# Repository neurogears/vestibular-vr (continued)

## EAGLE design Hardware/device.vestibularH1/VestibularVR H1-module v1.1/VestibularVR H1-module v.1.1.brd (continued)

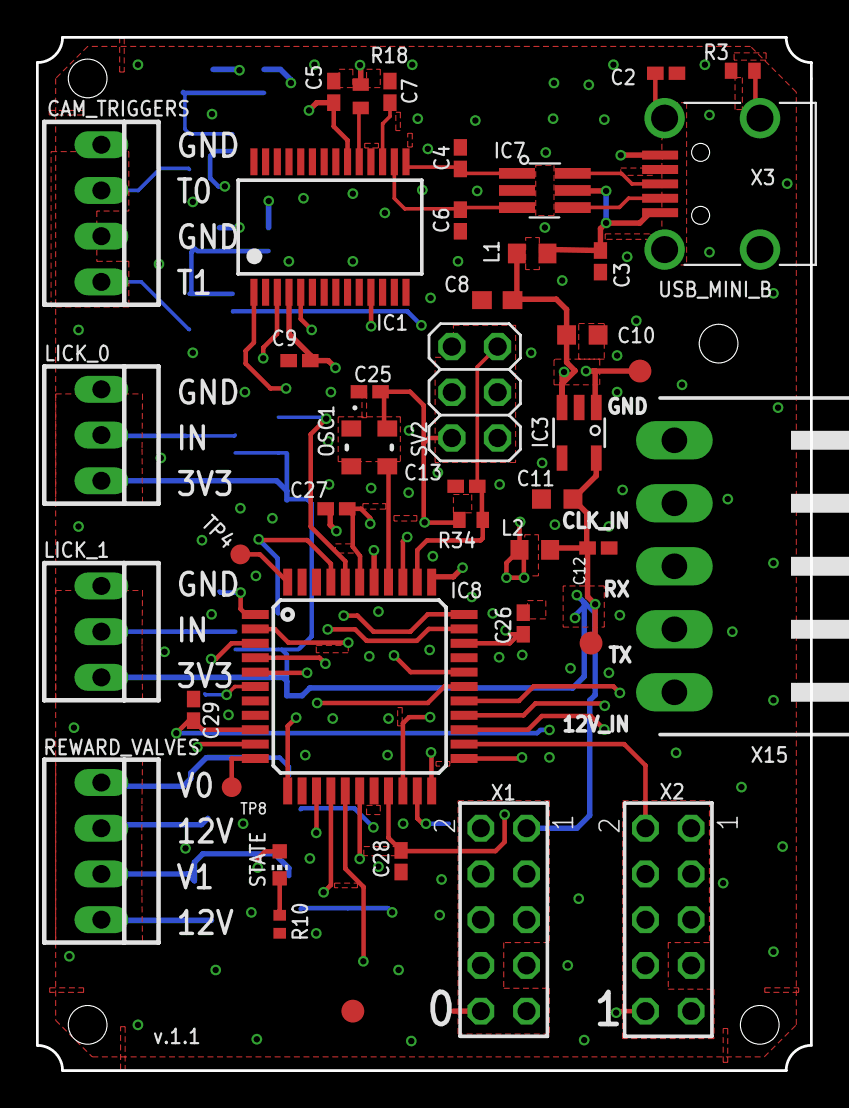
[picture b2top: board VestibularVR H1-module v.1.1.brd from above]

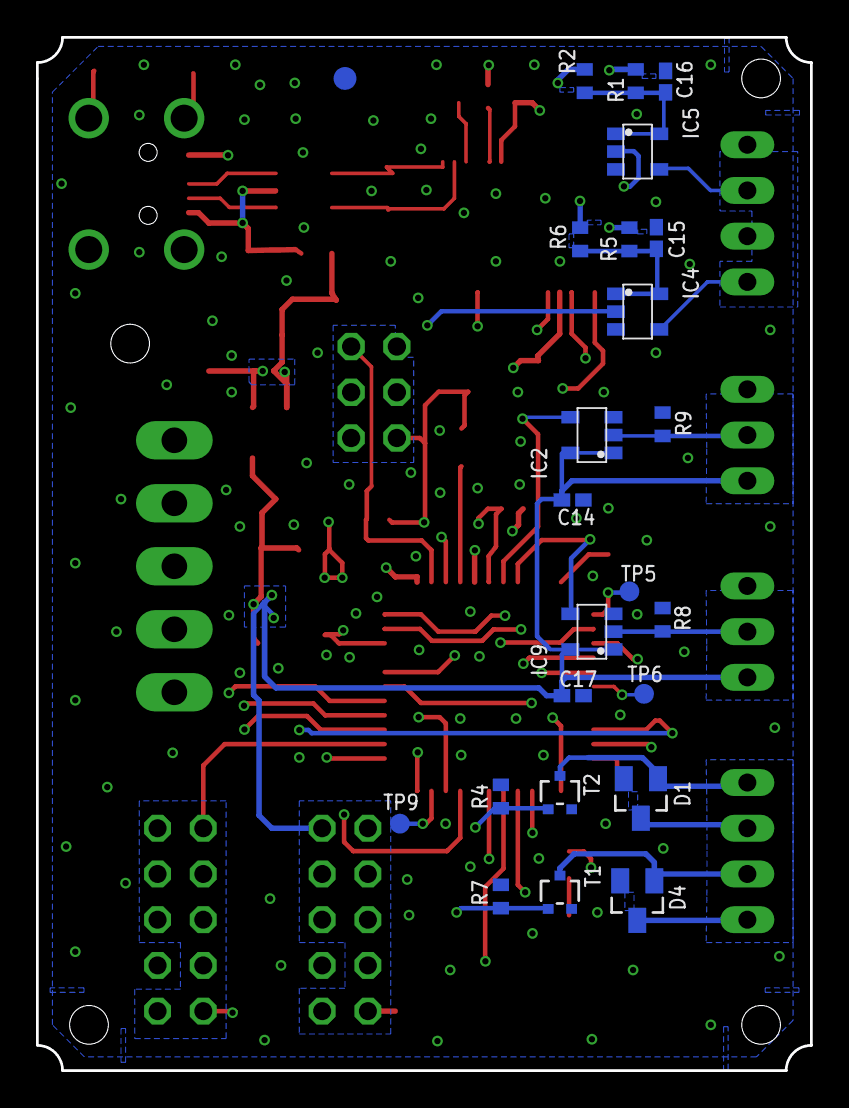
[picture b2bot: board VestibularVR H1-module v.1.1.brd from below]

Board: 4 copper layers, 43.0 x 57.4 mm, 67 parts (24 on the bottom side), 55 nets.

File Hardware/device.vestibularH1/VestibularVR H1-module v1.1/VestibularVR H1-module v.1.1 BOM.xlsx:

VestibularVR H1-module v.1.1 BOM
Qty | Parts | Value | OEPS | MPN | Device | Package | Description
2 | C10, C11 | 4.7uF | OEPS010018 | C1608X6S1C475K080AC | C-EUC0603K | C0603K | CAPACITOR, European symbol
1 | C2 | 4.7nF | OEPS010001 | CC0402KRX7R8BB472 | C-EUC0402K | C0402K | CAPACITOR, European symbol
14 | C3, C5, C7, C9, C12, C14, C15, C16, C17, C25, C26, C27, C28, C29 | 100nF | OEPS010004 | C1005X7R1H104K050BB | C-EUC0402K | C0402K | CAPACITOR, European symbol
3 | C4, C6, C13 | 47pF | n.a. | 04025A470JAT2A | C-EUC0402K | C0402K | CAPACITOR, European symbol
1 | C8 | 4.7uF | OEPS010018 | C1608X6S1C475K080AC | C-EUC0603 | C0603 | CAPACITOR, European symbol
2 | CAM_TRIGGERS, REWARD_VALVES | 1x4 case | OEPS070036 | 282834-4 | 22-23-2041 | 22-23-2041 | .100 (2.54mm) Center Header - 4 Pin"
2 | D1, D4 | BAT54 | OEPS030003 | BAT54SLT1G | BAT54 | SOT23 | Schottky Diodes
1 | IC1 | FT232RL | OEPS080013 | FT232RL | FT232RL | SSOP28 | UART/FIFO IC
4 | IC2, IC4, IC5, IC9 | M74VHC1GT126DT1G | OEPS080017 | M74VHC1GT126DT1G | M74VHC1GT126DT1G | TSOP-5 | Single Buffer/Driver With Open-Drain Output
1 | IC3 | LP5907MFX-3.3 | OEPS080016 | LP5907MFX-3.3/NOPB | TLV700XX | TSOT23-5 | C REG LINEAR 3.3V 200MA SOT23-5
1 | IC7 | USBLC6-2SC6 | OEPS030010 | USBLC6-2SC6 | USBLC6-2SC6 | SOT23-6L | TVS DIODE 5.25VWM 17VC SOT23-6
1 | IC8 | ATXMEGA32A4U | OEPS080012 | ATXMEGA32A4U-AUR | XMEGA-A4_AT-XMEGA-XXA4-AUTQFP44 | TQFP44 | ATxMega a4 Serie
2 | L1, L2 | 40R@100MHz | OEPS040003 | MI0805K400R-10 | R-EU_R0603 | R0603 | RESISTOR, European symbol
2 | LICK_0, LICK_1 | 1x3 case | OEPS070035 | 282834-3 | 22-23-2031 | 22-23-2031 | .100 (2.54mm) Center Header - 3 Pin"
1 | OSC1 | OSCILLATOR | OEPS080018 | DSC1001CI5-032.0000 | OSCILLATOR | OSCILLATOR_3.2X2.5 | XTAL OSC TCXO 32.0000MHZ HCMOS
2 | R1, R5 | 0R | OEPS020001 | RC0402JR-070RL | R-US_R0402 | R0402@1 | RESISTOR, American symbol
1 | R10 | 330R | OEPS020037 | RC0402FR-07330RL | R-EU_R0402 | R0402 | RESISTOR, European symbol
2 | R2, R6 | DNI | DNI | DNI | R-US_R0402 | R0402@1 | RESISTOR, American symbol
3 | R3, R8, R9 | 1M | OEPS020026 | CRCW04021M00FKED | R-US_R0402 | R0402@1 | RESISTOR, American symbol
4 | R4, R7, R18, R34 | 10k | OEPS020030 | CRCW040210K0FKED | R-US_R0402 | R0402@1 | RESISTOR, American symbol
1 | STATE | GREEN_LED | OEPS030005 | LTST-C191KGKT | LEDCHIP-LED0603 | CHIP-LED0603 | LED
1 | SV2 | PINHD-2X3 | OEPS070015 | 609-3210-ND | PINHD-2X3 | 2X03 | PIN HEADER
2 | T1, T2 | DMG1012UW | OEPS060010 | DMG1012UW-7 | DMG1012UW-7 | SOT323 | N-CHANNEL ENHANCEMENT MODE MOSFET
2 | X1, X2 | 2x5 header | n.a. | 2x5 header | TSW-105-02-S-D | TSW-105-02-S-D | THROUGH-HOLE .025 SQ POST HEADER"
1 | X15 | Main_plug | OEPS070037 | 20.155MH/5-E | 90G-5 | 90G-5 | WEIDMUELLER CLAMP CONNECTOR
1 | X3 | USB_MINI_B | OEPS070021 | UX60-MB-5S8 | USB_MINI_B | 240-0002-1 | CONN RCPT USB2.0 MINI B SMD R/A
.off board
Qty | Value | Parts | OEPS | Device | MPN | Package | Description
1 | CONN RCPT 10POS IDC 28AWG | n.a. | OEPS070040 | - | 1658621-1 AKC10H-ND | 2x5 10mil pitch | IDC 2x5 10mil pitch
1 | PAA5100JE Near Optical Flow Camera SPI Breakout | n.a. | OEPS ?? | - | PAA5100JE | - | PAA5100JE-Q is PixArt Imaging's latest optical navigation chip
2 | Lick Sensor module v1.0 PCB | n.a. | OEPS ?? | - | Lick Sensor module v1.0 | - | Lick Sensor
1 | Pluggable Terminal Block, 3.5 mm, 5 Ways | n.a. | OEPS070038 | - | 20.1550M/5-E Farnell 2575218 | - | External Terminal Block
n | flat ribbon cable | n.a. | OEPS090003 | - | 3365/10-100SF | - | RIBON 10COND 28AWG GRAY 100FT 30.48metter

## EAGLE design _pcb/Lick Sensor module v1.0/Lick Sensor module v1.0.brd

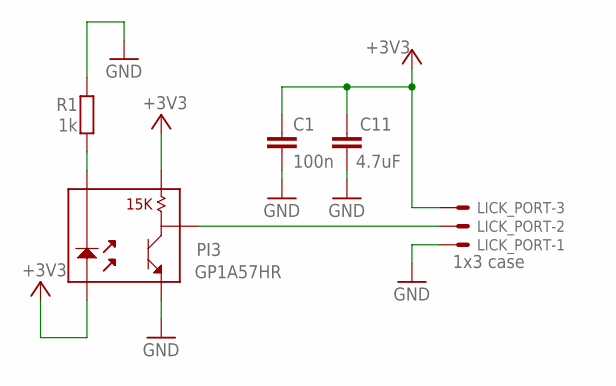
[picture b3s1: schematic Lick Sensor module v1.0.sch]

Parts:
C1: 100n; C0402K; MPN GRM155R71E104KE14D
C11: 4.7uF; C0603; MPN C1608X6S1C475K080AC
LICK_PORT: 1x3 case; 22-23-2031; MPN 282834-3
PI3: GP1A57HR; MPN GP1A57HRJ00F
R1: 1k; R0603; MPN ERJ-2RKF1001X

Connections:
+3V3: C1.1, C11.1, LICK_PORT.3, PI3.1, PI3.3
GND: C1.2, C11.2, LICK_PORT.1, PI3.5, R1.2
unnamed: LICK_PORT.2, PI3.4
unnamed: PI3.2, R1.1

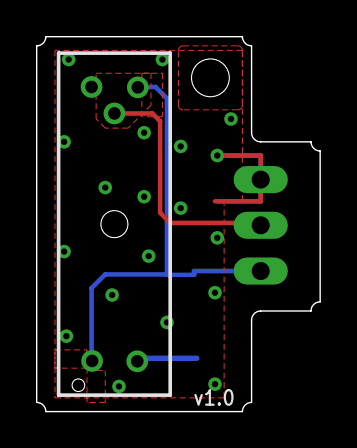
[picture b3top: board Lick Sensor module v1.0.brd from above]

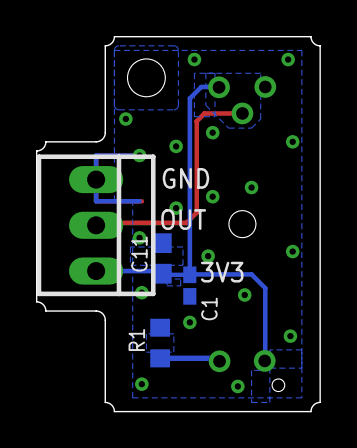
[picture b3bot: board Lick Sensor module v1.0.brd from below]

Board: 2 copper layers, 15.7 x 20.8 mm, 5 parts (4 on the bottom side), 4 nets.

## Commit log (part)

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2023-08-31 Testing relative movement
2023-08-31 Testing speed parameter setting
2023-09-01 Updated to use upgraded NewScale interface
2023-09-05 Upgrade package and test new features
    linked speeds, flipped directions
2023-09-08 Upgraded NewScale package for requested visualizer features
    See issue #14 for requested changes
2023-09-12 Fixing shader workflow errors
2023-09-12 Probe visualizer prototype
2023-09-20 Update to latest ONIX package
    Built from source
2023-09-20 Proper closing of draw quad SelectMany
2023-09-20 Cleanup screen sync test
2023-09-21 Data collection for roundtrip
2023-10-13 Basic cubemap rendering
2023-10-17 Add proto tracking of current position and rotation
2023-10-17 Cleanup layout
2023-10-17 Working 3d translation, movement
2023-10-19 Correct sphere mapping prototype
2023-10-20 Config for python runtime testing
2023-10-24 Revert bonsai version for testing gratings
2023-10-25 Virtual grating movement in 1D
2023-10-26 Update parameters for 4-screen surround
2023-10-26 create insertion workflow, add neuropixels shader window visualizer
2023-10-26 Add stacked LFP and spike visualizers
2023-10-30 Completed logging workflow for insertion workflow
2023-10-31 Remove unnecessary planning files, streamline to Bonsai project
2023-10-31 Prototype schema implementation
2023-10-31 Implement prototype loading of session settings
2023-11-02 Prototype for trial sequence
2023-11-02 Example trial stimulus drawing
2023-11-02 Cleanup workflow
2023-11-02 Example gratings settings in schema
2023-11-02 Added dummy movement feedback
2023-11-02 Cleanup DoTrial logic
2023-11-03 Outline trial logic state machine
2023-11-03 Initial run threshold logic
2023-11-03 Rewrite initial trial logic
2023-11-06 Add halt running check
2023-11-06 Use trial halt probability for trial type randm choice
2023-11-06 Ignore jetbrains files
2023-11-22 Completed analysis scripts for video benchmarks
2023-11-30 Update benchmark workflows for Matrox only test
2023-11-30 Updated round trip analysis script for updated data
2023-11-30 Add data for 60hz
2023-11-30 Ignore idea files
2023-11-30 Added PMW3360 test workflow
2023-12-05 Removing obsolete FilterMessage
2023-12-05 Remove other obsolete FilterMessage
2023-12-05 Testing proportional control with PMW3360
2023-12-08 Template workflow for motion clouds
2023-12-08 Basic playback of motion clouds
2023-12-11 update gitignore to ignore image textures
2023-12-13 Update schema for block centric parameters
2023-12-13 Add workflow for testing template loading
2023-12-14 Example session template with new schema
2023-12-14 Add decay timestep as schema parameter
2023-12-14 Correct timer initialization from session settings
2024-01-05 Halt trial type decision state
2024-01-05 Use experiment events instead of DrawText calls
2024-01-10 Reset threshold distance calculation on each loop
2024-01-10 Block reset on timer expiration
2024-01-10 Add random halt delay
2024-01-10 Tidy up components in group workflows
2024-01-10 Remove obsolete trial logic code
2024-01-10 Initial logic for block visual stimulus selection
2024-01-10 Testing visual stimulus switch
2024-02-06 Minimal debug and basic analysis script
2024-02-08 Initial workflow and layout for debugging analog IO
2024-02-08 Completed analog IO debug workflow
2024-02-08 Add delay subscription test to debug analog IO bug
2024-02-08 Decouple IO initialisation from data streaming
2024-02-14 Externalise session settings to be editable in main workflow
2024-02-14 Add flow sensor input as movement delta source
2024-02-14 Added prototype motion cloud block to trial logic
2024-02-15 Add vestibularH1 interface package
2024-02-15 Add camera control logic
2024-02-15 Add motion cloud 'corridor' to visual env
2024-02-15 Modify schema to allow for block specific gain
2024-02-15 Restore fullscreen settings for demo
    Also added simple visualizer for experiment events
2024-02-27 Retesting propotional control workflow with PMW3360
2024-02-27 Add nuget version of aeon package
2024-02-27 Fix configure bug in local Aeon SpinnakerCapture
2024-02-27 Add Aeon style SpinnakerCapture
2024-02-27 Restore trial logic
2024-02-27 Add H2 interface as local package
2024-02-27 Replace dynamic HARP operators for H2 hardware
2024-02-27 Replace initialisation HARP operators for H2 hardware
2024-02-27 Test workflow with new operators
2024-04-03 Add a start logging key option
2024-04-03 Add experiment event for start logging
2024-04-04 Update schema to include further gain settings
2024-04-04 Add basic H2 device logic
2024-04-04 Add initial H2 reset
2024-04-04 Initial block type example with inheritance
2024-04-04 Testing instantiation of block types
2024-04-04 Update schema to provide vis stim extents as well as offsets
2024-04-04 Update stimulus fields with schema parameters
2024-04-09 Add mouse wheel input for debug
2024-04-09 Add alias property to schema
2024-04-09 Generate interface for new schema
2024-04-09 Create variable source for block gain
2024-04-09 Modifiable visual flow sources
    FlowX, FlowY, rotarty motion and playback source all contribute to phase procession, according to gain set in schema.
2024-04-09 Initial motor procession calculation
2024-04-09 Creation of motor pulse command
2024-04-10 Testing motor control with new schema parameters
2024-04-10 Use CombineLatest for motor procession calculation
2024-04-10 Remove mouse wheel debug
    Dangerous while motor is turned on!
2024-04-10 Add homing functionality
    Added homing command, CW and CCW step commands. Home platform on each block.
2024-04-10 Testing new block logic
2024-04-30 visual stimuli workflows
2024-05-03 npx new workflows and bonsai config
2024-05-03 npx new workflows
2024-05-03 test fokder
2024-05-03 syncronize
2024-05-04 added matrix writer nodes and headstage port control
2024-05-04 np1.0 headstage workflow for streaming and saving
2024-05-04 file organisation
2024-05-06 correct Sync workflow
2024-05-07 Sync workflow for test
2024-05-10 wallpaper
2024-05-10 corridor_FOE
2024-05-10 cam trigger 30 hz
2024-05-10 spatial freq
2024-05-16 INFINITE CORRIDOR_FOE
2024-05-17 H1 com switch
2024-05-17 change fs and triggwidth
2024-06-04 switched COMs in Main
2024-06-05 schema updated
2024-06-05 disabled ttl
2024-06-05 corridor stimulus initial commit
2024-06-07 orthopgraphic view
    Set spatial frequency as total number of cycles per 360 degrees
2024-06-12 new insertion workflow
2024-06-13 changes in insertion workflow
2024-06-19 hilde sync test_ removed start key press
2024-06-19 openephys socket test
2024-06-26 motor_gain_test_yml_files
2024-06-27 Update local schema for named array payload
2024-07-02 Add prototype test workflow for screen sync quad logic
2024-07-03 motor test gain yml with ede
2024-07-09 yml file org
2024-07-09 Initial sampling test
2024-07-09 Prototype logic for photometry sync
2024-07-09 Add logging for ONIX streams
2024-07-11 Fix halt event placement
2024-07-11 Revert back from mouse wheel debug
2024-07-18 Alternate motor signal sampling approach
2024-07-18 Blocks return a value only when complete
2024-07-19 Longer initial runtime for testing
2024-07-19 Testing sync quad in main workflow
2024-07-19 Basic playback file conversion script
2024-07-19 Proto cleanup
2024-07-19 Update schema with playback file
2024-07-19 Reimplement playback source
2024-07-19 Testing playback source
2024-07-19 Update data schema extension
2024-07-19 Add run gains to main workflow
2024-07-23 Add experiment event logging
2024-07-26 changed quad position
2024-07-26 updated training session yml
2024-08-12 Initial documentation
2024-08-12 Environment documentation
2024-08-12 Schema specifics documentation
2024-08-12 Complete basic setup documentation
2024-09-13 main_workflow_screensyncquad
2024-09-16 Initialise motor playback with 0
2024-09-16 Add temp data paths
2024-09-16 Add a notebook for photometry sync examples
2024-09-17 Use aeon api for device loading
2024-09-19 Onix timestamp mapping
2024-09-19 Photometry stream reader
2024-09-19 Notes for next steps
2024-09-20 Add aligned photometry to figure
2024-09-20 Add new ONIX packages
2024-09-20 Update layout for main visualizer
2024-09-24 Remove defunct local packages
2024-09-24 Add a better harp sync monitor
2024-09-24 Update motion cloud test with named texture
2024-09-24 Add texture folder extension to main workflow
2024-09-24 Update schema for named texture rather than path
2024-09-24 Example texture file loading
2024-09-25 Modify regression for onix synchronisation
2024-09-26 Simple notebook for encoder vs. flow sanity check
2024-09-26 Subscribe to raw and buffer analog streams simultaneously
2024-09-27 Example access of texture sequence data
2024-09-27 Add extra example texture to TextureResources
2024-09-27 Add test schema for switching motion clouds
2024-09-27 Divide by zero checking
2024-10-03 Fix initial texture data loading bug
2024-10-03 Add smoother movement delta to main workflow
2024-10-16 Fix texture frame initialisation bug
    If a longer texture is initially loaded, followed by a shorter one, BindTexture will initially try and load the last indexed frame which may be out of bounds of the longer texture length. Fix by alwa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
2024-10-16 Testing playback with motion clouds
2024-10-16 Example generating a valid sin wave playback file
2024-10-16 Update prepare-playback_file and test
2024-10-16 Revert back from debug movement delta
2024-10-19 linear_drift_playback
2024-10-19 new yml for rotation
2024-10-19 int16 conversion
2024-10-19 update smooth int16 drift
2024-10-19 drift
2024-10-19 10000
2024-10-22 new playback
2024-10-22 yml files
2024-10-31 Added some example schemas for different playback blockls
2024-10-31 Update schema to allow for more control over delta switches
2024-10-31 Implement reverse halt attempt
2024-10-31 Implement reverse halt and fix delta setting in ApplyHalth
2024-10-31 Revert from debug motion mode
2024-10-31 Add motion smoothing parameter to schema
2024-10-31 Implement flow smoothing in main workflow
2024-10-31 Add schema parameters for cameras to main workflow
2024-10-31 Update aeon package and add gain parameters to cameras
2024-11-14 Interval latency test
2024-11-15 Add initial analysis script
2024-11-15 Mean and std analysis for pulse to encoder time
2024-11-15 Full latency analysis
2024-12-18 Remove comma in experiment event
2025-01-09 Log digital input state as integer rather than enum
2025-01-13 yml_workflow_changes
2025-01-15 Update postprocessing script for new digital input bitmask logging
2025-01-15 Revert Aeon package and remove gain parameters
2025-01-15 Minimal notebook to try and reproduce bug
2025-01-16 Add python environment instructions to readme
2025-01-16 Fix readme typo
2025-01-23 Fix pulses initiation issue
2025-02-05 added .DS_Store to gitignore
2025-02-06 workflow and drivers
2025-02-07 wf changes
2025-02-12 Enable heartbeats in Harp devices
2025-02-13 new yml files and change in screen res on main wf
2025-02-17 added cloud to textures, removed old one.
2025-02-24 Ignore sleap files
2025-02-24 Remove hubclock logging from main workflow
2025-02-26 Revert "added heartbeat to H1 and H2 .yml files"
2025-02-27 Add initial workflow for arena
2025-02-27 Add basic screen mapping
2025-03-06 Rotation calculations
2025-03-06 Translation calculations
2025-03-06 Only need to do forward vector calculation
2025-03-06 Add views for all 4 screens
2025-03-06 Add some models and placements
2025-03-06 Prototype arena
2025-03-10 use encoder reading to affect forward vector
2025-03-11 Add position limits for arena
2025-03-11 Testing model drawing in arena
2025-03-11 Add screen sync quad
2025-03-11 Testing screen sync quad
2025-03-11 Logging of current relevant data streams
2025-03-12 Fix S16 overflow in encoder diff values
2025-03-12 Overflow difference operator
2025-03-12 Add environment objects
2025-03-17 Add logging for position and forward vector
2025-04-18 Notes on data acquisition
2025-04-18 Notes on gain settings
2025-04-18 Flow sensor smoothing notes
2025-04-18 Homing speed settable as part of schema
2025-04-21 Sleap training steps
2025-04-21 Sleap example
2025-04-23 Fix key down subscription for trial logic
2025-04-23 yml change
2025-04-29 new ymll file
2025-04-30 new yml
2025-10-01 new yml
    added yml file to src to be used in next experiments
2025-11-29 Update README.md
    with current Spinnaker download path
2025-12-02 added timestamp diff visualisers for cameras
2025-12-02 added brightness histogram for flow sensor
